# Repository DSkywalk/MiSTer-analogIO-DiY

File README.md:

# MiSTer-analogIO-DiY

The aim of this repository is to share boards that can be easily crafted at home (ex. Electric iron) for MiSTer FPGA enthusiasts. No SMD and trying to use almost one layer...

Of course, you can order these boards from OSHPark or any other PCB printing company, but that is not the main purpose of this repository.

This is my first project using Kicad, contributions are very welcome :+1:

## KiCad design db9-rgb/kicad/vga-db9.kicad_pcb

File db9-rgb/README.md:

# RGB + DB9 + MIDI

### 1. Order PCB

#### Some PCB Manufactors
  * [OSH Park](https://oshpark.com/)
  * [PCBway](https://www.pcbway.com/)
  * [JLCPCB](https://jlcpcb.com/)

### 2. Order Components

This is a bill of materials to assemble an AnalogIO Board.

| Qty | Name | Component | Value | Reference Parts | Notes |
|---|---|---|:---:|---|---|
| 1 | CONNECTOR_... | Pin header 2.54mm 1x20 |  | [rs](https://uk.rs-online.com/web/p/pcb-headers/2518632/) [ebay-kit](https://www.ebay.co.uk/itm/SKY/192534020920) | some optional |
| 1 | MiSTer1 | Pin header 2.54mm 2x20 |  | [rs](https://uk.rs-online.com/web/p/pcb-headers/6703496/) [ebay](https://www.ebay.co.uk/itm/yavi/253239947055) | optional, you could use two 1x20 |
| 16 | D1...D16 | Schottky Diode - 30V 200mA | BAT42 / BAT42-TR | [rs](https://uk.rs-online.com/web/p/rectifier-diodes-schottky-diodes/5444758P/) | |
| 10 | HSYNC1, VSYNC1, DB9_1...8 | Resistor 1% / 5% 0.6W | 100 | [rs](https://uk.rs-online.com/web/p/through-hole-fixed-resistors/0148433/) [ebay-kit](https://www.ebay.es/itm/SKY/383379552017) | |
| 3 | RED_1, GRE_1, BLU_1 | Resistor 1% 0.6W | 510 | [rs](https://uk.rs-online.com/web/p/through-hole-fixed-resistors/0148433/) | |
| 3 | RED_2, GRE_2, BLU_2 | Resistor 1% 0.6W | 1.1K | [rs](https://uk.rs-online.com/web/p/through-hole-fixed-resistors/0148512/) | |
| 3 | RED_3, GRE_3, BLU_3 | Resistor 1% 0.6W | 2.2K | [rs](https://uk.rs-online.com/web/p/through-hole-fixed-resistors/6833449/) | |
| 3 | RED_4, GRE_4, BLU_4 | Resistor 1% 0.6W | 4.3K | [rs](https://uk.rs-online.com/web/p/through-hole-fixed-resistors/0148657/) | |
| 3 | RED_5, GRE_5, BLU_5 | Resistor 1% 0.6W | 9.1K | [rs](https://uk.rs-online.com/web/p/through-hole-fixed-resistors/0148720/) | |
| 3 | RED_6, GRE_6, BLU_6 | Resistor 1% 0.6W | 18K | [rs](https://uk.rs-online.com/web/p/through-hole-fixed-resistors/0148792/) | |

### 3. Optional Components
#### 3.1 SPDIF using LED

| Name | Component | Value | Reference Parts |
|---|---|:---:|---|
| SPDIF1 | LED 5mm | Red | [rs](https://uk.rs-online.com/web/p/products/2285988/) |
| DIG1 | Resistor 1% / 5% 0.6W | 200 | [rs](https://uk.rs-online.com/web/p/through-hole-fixed-resistors/0132321/) |
| DUMMY JACK | Socket Audio Jack Connector PCB 5Pin | 3F07 | [ali](https://www.aliexpress.com/item/32694891007.html) | 

#### 3.2 SPDIF using TOSLINK

| Name | Component | Value | Reference Parts |
|---|---|:---:|---|
| C1 | Capacitor (Ceramic) 0104 / 0105 | 1uF / 0.1uF | [rs](https://uk.rs-online.com/web/p/mlccs-multilayer-ceramic-capacitors/5381578/) |
| SPDIF_CON1 | Audio Fiber-Optic Terminal 03B | DLT-11E0 | [ali](https://www.aliexpress.com/item/4000333102343.html) |

#### 3.3 DB9 using PCB Socket

| Name | Component | Value | Reference Parts |
|---|---|:---:|---|
| DB9 | DSUB 90º |  | [rs](https://uk.rs-online.com/web/p/d-sub-connectors/2395855/) |

#### 3.4 DB9 using J9 Connector

| Name | Component | Value | Reference Parts |
|---|---|:---:|---|
| DB9 | DSUB |  | [rs](https://uk.rs-online.com/web/p/d-sub-connectors/5443749/) |

### 4. Other Options
#### 4.1 J1 Conector / EXTRA LED

These LEDs are completely optional, you can see them on the board itself, if you want to connect them to have them visible externally you will also need some 200ohm resistors. And connect them to GND like any other LED.

* U: LED USR
* U: LED DISK
* U: LED POWER

#### 4.2 J2 Conector / EXTRA BUTTONS

These buttons are completely optional, you can do the same operations using any controller. Connect them to GND.

* U: BTN OSD
* U: BTN USER
* U: BTN RESET

### 5 RGB
#### 5.1 VIDEO_EXT

This connector is commonly used for graphics with a VGA connector. Or you can solder your own.

| PIN | Name |
|---|---|
| 1 | RED |
| 3 | GREEN |
| 5 | BLUE |
| 2, 4 | GND |
| 10 | HSYNC (or H+V using JP1) |
| 11 | VSYNC |
| 8  | LOCKED/BLIND |
| 6,7,9,12 | NC |

#### 5.3 Useful Information

* HSYNC1 & VSYNC1 are attenuated with a 100-ohm resistance. You could use a variable resistor if you know your TV can be problematic or test other values.
* SWITCH PIN1: 3.3V You could use this connector as TV RGB SWITCH.
* SWITCH PIN2: 5V You could use this connector as TV AV SWITCH.

### 6 Notes
#### 6.1 JP1 / SYNC

Join this pin if you want to combine HSYNC and VSYNC or you prefer to have them separate, for PC-VGA separate them and for TV combine them.

#### 6.2 EX Heads

* JP1x01 5V, VCC (3.3V), GND: Ready for your usage.
* 5V1 JP_1x02: 5V + GND: Ready for your usage.
* 3.3V1 JP_1x02: 3.3V + GND: Ready for your usage.

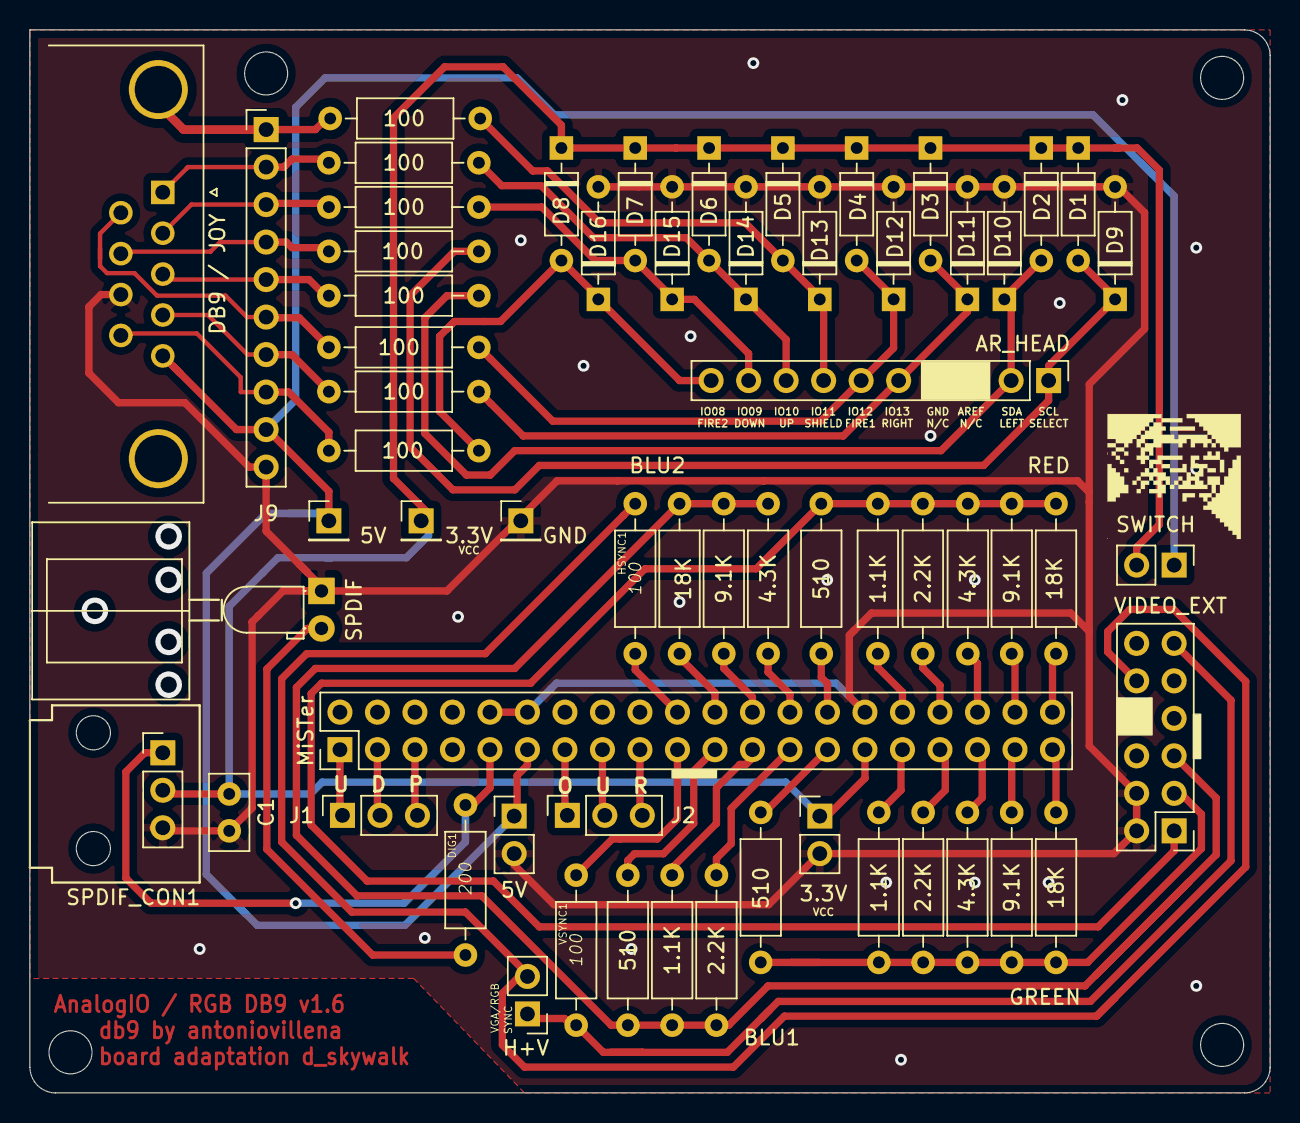
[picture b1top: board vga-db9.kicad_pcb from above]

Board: 2 copper layers, 84.0 x 72.0 mm, 62 parts (0 on the bottom side), 52 nets.

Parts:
3.3V: 3V; PinHeader_1x01_P2.54mm_Vertical
3.3V#2: RGB-SWITCH; PinHeader_1x02_P2.54mm_Vertical
5V: 5V; PinHeader_1x01_P2.54mm_Vertical
5V#2: AV; PinHeader_1x02_P2.54mm_Vertical
AR_HEAD: 10; PinHeader_1x10_P2.54mm_Vertical
BLU_1: 18K; R_Axial_DIN0207_L6.3mm_D2.5mm_P10.16mm_Horizontal
BLU_2: 9.1K; R_Axial_DIN0207_L6.3mm_D2.5mm_P10.16mm_Horizontal
BLU_3: 4.3K; R_Axial_DIN0207_L6.3mm_D2.5mm_P10.16mm_Horizontal
BLU_4: 2.2K; R_Axial_DIN0207_L6.3mm_D2.5mm_P10.16mm_Horizontal
BLU_5: 1.1K; R_Axial_DIN0207_L6.3mm_D2.5mm_P10.16mm_Horizontal
BLU_6: 510; R_Axial_DIN0207_L6.3mm_D2.5mm_P10.16mm_Horizontal
C1: 1uF/0.1uF; C_Disc_D5.0mm_W2.5mm_P2.50mm
D1, D2, D3, D4, D5, D6, D7, D8, D9, D10, D11, D12, D13, D14, D15, D16: BAT42; D_DO-35_SOD27_P7.62mm_Horizontal
DB9 / JOY: DB9_Male; DSUB-9_Male_Horizontal_P2.77x2.84mm_EdgePinOffset4.94mm_Hou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
DB9_1, DB9_2, DB9_3, DB9_4, DB9_5, DB9_6, DB9_7, DB9_8: 100; R_Axial_DIN0207_L6.3mm_D2.5mm_P10.16mm_Horizontal
DIG1: 200; R_Axial_DIN0207_L6.3mm_D2.5mm_P10.16mm_Horizontal
GND: GND; PinHeader_1x01_P2.54mm_Vertical
GRE_1: 18K; R_Axial_DIN0207_L6.3mm_D2.5mm_P10.16mm_Horizontal
GRE_2: 9.1K; R_Axial_DIN0207_L6.3mm_D2.5mm_P10.16mm_Horizontal
GRE_3: 4.3K; R_Axial_DIN0207_L6.3mm_D2.5mm_P10.16mm_Horizontal
GRE_4: 2.2K; R_Axial_DIN0207_L6.3mm_D2.5mm_P10.16mm_Horizontal
GRE_5: 1.1K; R_Axial_DIN0207_L6.3mm_D2.5mm_P10.16mm_Horizontal
GRE_6: 510; R_Axial_DIN0207_L6.3mm_D2.5mm_P10.16mm_Horizontal
HSYNC1: 100; R_Axial_DIN0207_L6.3mm_D2.5mm_P10.16mm_Horizontal
J1, J2: Conn_01x03; PinSocket_1x03_P2.54mm_Vertical
J9: Conn_01x09; PinHeader_1x10_P2.54mm_Vertical
JP1: SYNC; PinHeader_1x02_P2.54mm_Vertical
MiSTer: Conn_02x20; PinHeader_2x20_P2.54mm_Vertical
RED_1: 18K; R_Axial_DIN0207_L6.3mm_D2.5mm_P10.16mm_Horizontal
RED_2: 9.1K; R_Axial_DIN0207_L6.3mm_D2.5mm_P10.16mm_Horizontal
RED_3: 4.3K; R_Axial_DIN0207_L6.3mm_D2.5mm_P10.16mm_Horizontal
RED_4: 2.2K; R_Axial_DIN0207_L6.3mm_D2.5mm_P10.16mm_Horizontal
RED_5: 1.1K; R_Axial_DIN0207_L6.3mm_D2.5mm_P10.16mm_Horizontal
RED_6: 510; R_Axial_DIN0207_L6.3mm_D2.5mm_P10.16mm_Horizontal
SPDIF: LED_RED; LED_D3.0mm_Horizontal_O1.27mm_Z2.0mm
SPDIF_CON1: Conn_alt; PinHeader_1x03_P2.54mm_Vertical
SWITCH: SYNC; PinHeader_1x02_P2.54mm_Vertical
VIDEO_EXT: Conn_02x06_Odd_Even; PinHeader_2x06_P2.54mm_Vertical
VSYNC1: 100; R_Axial_DIN0207_L6.3mm_D2.5mm_P10.16mm_Horizontal

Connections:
5V: 5V.1, 5V#2.1, DB9 / JOY.5, J9.9, MiSTer.11, SWITCH.1
/AE15-IO9: AR_HEAD.9, D7.2, D15.1, DB9_7.2
/AF15-IO10: AR_HEAD.8, D6.2, D14.1, DB9_6.2
/AF17-IO8: AR_HEAD.10, D8.2, D16.1, DB9_8.2
/AG11-IO15: AR_HEAD.1, D1.2, D9.1, DB9_1.2
/AG16-IO11: AR_HEAD.7, D5.2, D13.1, DB9_5.2
/AH9-IO14: AR_HEAD.2, D2.2, D10.1, DB9_2.2
/AH11-IO12: AR_HEAD.6, D4.2, D12.1, DB9_4.2
/AH12-IO13: AR_HEAD.5, D3.2, D11.1, DB9_3.2
DOWN: DB9 / JOY.2, DB9_7.1, J9.3
FIRE1: DB9 / JOY.6, DB9_4.1, J9.6
FIRE2: DB9 / JOY.9, DB9_8.1, J9.8
GND: 3.3V#2.2, 5V#2.2, C1.2, D9.2, D10.2, D11.2, D12.2, D13.2, D14.2, D15.2, D16.2, DB9 / JOY.8, GND.1, J9.10, MiSTer.10, MiSTer.12, MiSTer.30, SPDIF.1, SPDIF_CON1.3, VIDEO_EXT.2, VIDEO_EXT.4
LED_DISK: J1.2, MiSTer.3
LED_PWR: J1.3, MiSTer.5
LED_USR: J1.1, MiSTer.1
LEFT-CLK: DB9 / JOY.3, DB9_2.1, J9.5
MUX: DB9 / JOY.0, DB9_5.1, J9.1
unnamed: BLU_1.1, BLU_2.1, BLU_3.1, BLU_4.1, BLU_5.1, BLU_6.1, VIDEO_EXT.5
unnamed: BLU_1.2, MiSTer.22
unnamed: BLU_2.2, MiSTer.24
unnamed: BLU_3.2, MiSTer.26
unnamed: BLU_4.2, MiSTer.25
unnamed: BLU_5.2, MiSTer.23
unnamed: BLU_6.2, MiSTer.21
unnamed: DIG1.2, SPDIF.2
unnamed: GRE_1.1, MiSTer.39
unnamed: GRE_1.2, GRE_2.2, GRE_3.2, GRE_4.2, GRE_5.2, GRE_6.2, VIDEO_EXT.3
unnamed: GRE_2.1, MiSTer.37
unnamed: GRE_3.1, MiSTer.35
unnamed: GRE_4.1, MiSTer.33
unnamed: GRE_5.1, MiSTer.31
unnamed: GRE_6.1, MiSTer.27
unnamed: HSYNC1.1, MiSTer.20
unnamed: HSYNC1.2, JP1.2, VIDEO_EXT.10
unnamed: JP1.1, VIDEO_EXT.11, VSYNC1.2
unnamed: MiSTer.19, VSYNC1.1
unnamed: MiSTer.28, RED_6.1
unnamed: MiSTer.32, RED_5.1
unnamed: MiSTer.34, RED_4.1
unnamed: MiSTer.36, RED_3.1
unnamed: MiSTer.38, RED_2.1
unnamed: MiSTer.40, RED_1.1
unnamed: RED_1.2, RED_2.2, RED_3.2, RED_4.2, RED_5.2, RED_6.2, VIDEO_EXT.1
OSD: J2.1, MiSTer.13
RESET: J2.3, MiSTer.17
RIGHT: DB9 / JOY.4, DB9_3.1, J9.7
SELECT-LAT: DB9 / JOY.7, DB9_1.1, J9.4
SPDIFF: DIG1.1, MiSTer.9, SPDIF_CON1.1
UP-DAT: DB9 / JOY.1, DB9_6.1, J9.2
USER: J2.2, MiSTer.15
VCC: 3.3V.1, 3.3V#2.1, C1.1, D1.1, D2.1, D3.1, D4.1, D5.1, D6.1, D7.1, D8.1, MiSTer.29, SPDIF_CON1.2, SWITCH.2

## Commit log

2020-08-02 db9 v1.0
2020-08-02 db9 - base files
2020-08-02 fix JP1 size
2020-08-02 update sync / new tv switch connector
2020-08-21 fixed resistors and spdif.
2021-05-02 upgraded to 1.6 - removed midi old, now using db9
2021-05-03 changed AR_HEAD order
2021-05-03 fix size gfx
2021-05-03 updated sheet
